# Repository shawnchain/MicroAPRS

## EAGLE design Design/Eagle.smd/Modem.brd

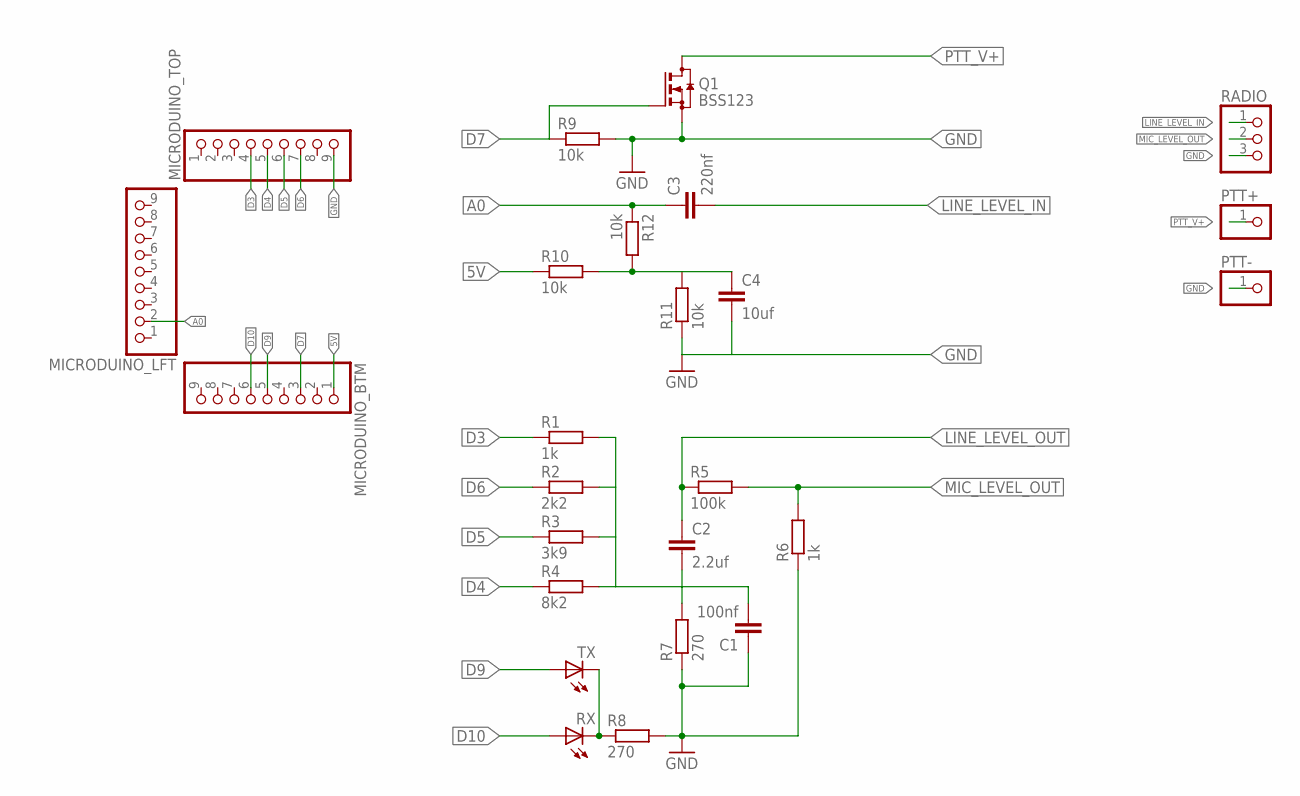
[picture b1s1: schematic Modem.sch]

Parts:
C1: 100nf; C0603
C2: 2.2uf; C1206
C3: 220nf; C0603
C4: 10uf; C1206
MICRODUINO_BTM: PINHD-1X9; 1X09-BIG
MICRODUINO_LFT: PINHD-1X9; 1X09-BIG
MICRODUINO_TOP: PINHD-1X9; 1X09-BIG
PTT+: PINHD-1X1; 1X01
PTT-: PINHD-1X1; 1X01
Q1: BSS123; SOT23
R1, R6: 1k; R0603
R2: 2k2; R0603
R3: 3k9; R0603
R4: 8k2; R0603
R5: 100k; R0603
R7, R8: 270; R0603
R9, R10, R11, R12: 10k; R0603
RADIO: PINHD-1X3; 1X03
RX: LED_E; LED_1206
TX: LED_E; LED_1206

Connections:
5V: MICRODUINO_BTM.1, R10.1
A0: C3.1, MICRODUINO_LFT.2, R12.1
D3: MICRODUINO_TOP.4, R1.1
D4: MICRODUINO_TOP.5, R4.1
D5: MICRODUINO_TOP.6, R3.1
D6: MICRODUINO_TOP.7, R2.1
D7: MICRODUINO_BTM.3, Q1.1 (G), R9.1
D9: MICRODUINO_BTM.5, TX.A
D10: MICRODUINO_BTM.6, RX.A
GND: C1.1, C4.2, MICRODUINO_TOP.9, PTT-.1, Q1.2 (S), R6.1, R7.1, R8.2, R9.2, R11.1, RADIO.3
LINE_LEVEL_IN: C3.2, RADIO.1
LINE_LEVEL_OUT: C2.1, R5.1
MIC_LEVEL_OUT: R5.2, R6.2, RADIO.2
unnamed: R8.1, RX.C, TX.C
unnamed: C1.2, C2.2, R1.2, R2.2, R3.2, R4.2, R7.2
unnamed: C4.1, R10.2, R11.2, R12.2
PTT_V+: PTT+.1, Q1.3 (D)

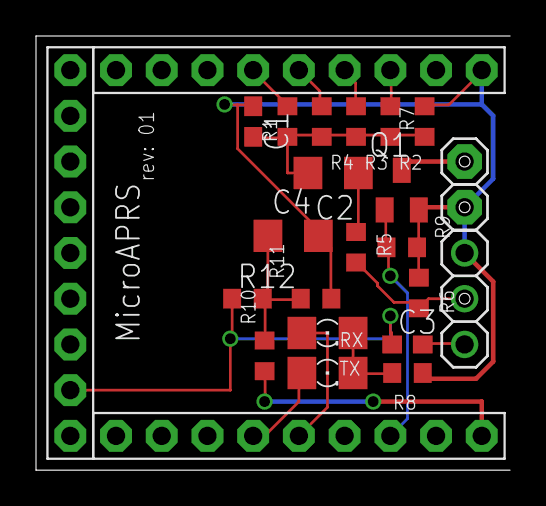
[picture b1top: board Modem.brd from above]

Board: 2 copper layers, 26.3 x 24.1 mm, 25 parts (0 on the bottom side), 17 nets.

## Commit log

2014-09-21 Add FIR filter
2014-09-23 Remove MODEM_DEBUG to slim down the hex size so that to run under ArduinoProMini
2014-09-26 Enable debug output, should compile under OSX
2014-09-27 Change PCB design to use SMD
2014-09-27 Add input filter
2014-09-28 Update images
